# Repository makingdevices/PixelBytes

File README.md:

<!-- Improved compatibility of back to top link: See: https://github.com/othneildrew/Best-README-Template/pull/73 -->

<!--
*** Thanks for checking out the Best-README-Template. If you have a suggestion
*** that would make this better, please fork the repo and create a pull request
*** or simply open an issue with the tag "enhancement".
*** Don't forget to give the project a star!
*** Thanks again! Now go create something AMAZING! :D
-->

<!-- PROJECT SHIELDS -->
<!--
*** I'm using markdown "reference style" links for readability.
*** Reference links are enclosed in brackets [ ] instead of parentheses ( ).
*** See the bottom of this document for the declaration of the reference variables
*** for contributors-url, forks-url, etc. This is an optional, concise syntax you may use.
*** https://www.markdownguide.org/basic-syntax/#reference-style-links
-->
[![Instagram][ig-shield]][ig-url]
[![PCBWAY][sponsor-shield]][sponsor-url]
[![Stargazers][stars-shield]][stars-url]
[![Issues][issues-shield]][issues-url]
[![LinkedIn][linkedin-shield]][linkedin-url]

<!-- PROJECT LOGO -->
<br />
<div align="center">

<h3 align="center">Making Devices</h3>

  <p align="center">
    Open Source projects where we struggle with engineering, electronics, coding and who knows what else... Pixel Bytes is an evolution of my previous 8-bit console. The new version is based in the STM32F103CB with IC Leds for a colorwide screen and new power to code new games. 
  </p>
</div>

<!-- TABLE OF CONTENTS -->
<details>
  <summary>Table of Contents</summary>
  <ol>
    <li>
      <a href="#about-the-project">About The Project</a>
      <ul>
        <li><a href="#built-with">Built With</a></li>
      </ul>
    </li>
    <li>
      <a href="#Build-one">Build one</a>
      <ul>
      </ul>
    </li>
    <li><a href="#usage">Usage</a></li>
    <li><a href="#roadmap">Roadmap</a></li>
    <li><a href="#license">License</a></li>
    <li><a href="#contact">Contact</a></li>
    <li><a href="#Sponsor">Sponsor</a></li>
  </ol>
</details>

<!-- ABOUT THE PROJECT -->
## About The Project

[![Bytes Counter Shot][product-screenshot]](https://makingdevices.com/)

PixelBytes was born in colaboration with Wurth Elektronik and their new RGB IC LEDs. They sent me a bunch of them to test so I though of making a proper evolution of my previous video console. For this time, I wanted to test a new manufacturer for the microcontroller, so it is my first big project working with the STM32. Hopefully it will help to develop new exciting games as it is arduino-compatible. On top of that, I decided to add a giroscope sensor so we can add more ways to have fun within the gaming experience ;). 

The project is divided into two steps: 
1. The first one is the PixelBytesDisplay, which is a matrix of 13x21 IC LEDs divided in 6 strings. 
2. The second part is the host board, which will mount the microcontroller and all the battery and sensors.

<p align="right">(<a href="#readme-top">back to top</a>)</p>

### Built With

[![Microcontroller][PIC]][PIC-url]
[![Arduino][Arduino]][Arduino-url]
[![Kicad][kicad-shield]][kicad-url]
[![SPONSOR][wurth-icon]][sponsor-url-wurth]
[![SPONSOR][sponsor-icon]][sponsor-url]

<p align="right">(<a href="#readme-top">back to top</a>)</p>

<!-- GETTING STARTED -->

## Build one
The project is yet to be finished. Should you want to reproduce it, be careful. 

1. Get the gerber files for the latest version: [Pixel Bytes Display V0.1](/Gerber/Display/pixelbytesdisplay-v0.1) 
2. Get the gerber files for the latest version: [Pixel Bytes Host V0.1](/Gerber/Host/PixelBytesHostV0.1) 
3. Send them to a PCB manufacturer ([Our Sponsor is PCBWAY][sponsor-url])

YET TO BE COMPLETED.

<p align="right">(<a href="#readme-top">back to top</a>)</p>

<!-- USAGE EXAMPLES -->
## Usage

Instructions of use:

- When turn on, a menu is shown to select between the available games.
- Once you have played a game, a score board will appear everytime you open the game.
- You have a setting menu to turn-off the init splash and the sound.
- If you leave the console one minute without touching the buttons, it will turn into sleep mode.
- Enjoy!

<p align="right">(<a href="#readme-top">back to top</a>)</p>

<!-- ROADMAP -->
## Roadmap

- [x] Validate the Pixel Bytes Display
- [x] Assembly a prototype with the F103 Board
- [ ] Order/Assembly the Pixel Bytes Host
- [ ] Develop the firmware
  - [ ] Develop the library for the screen
  - [ ] Develop the menu 
  - [ ] Develop Snake
  - [ ] Develop Arkanoid
  - [ ] Develop Tetris
  - [ ] Develop a game that uses the gyro sensor
  - [ ] Score board
  - [ ] Sleep Mode
- [ ] Validate the complete design (host + display board)

See the [open issues](https://github.com/makingdevices/PixelBytes/issues) for a full list of proposed features (and known issues).

State: Project <b>ONGOING</b> - 22/09/2024

Priority: <b>High</b>

<p align="right">(<a href="#readme-top">back to top</a>)</p>

<!-- LICENSE -->
## License

Distributed under three licenses:
- [Hardware](/License/HW_cern_ohl_s_v2.pdf)
- [Software](/License/SW_GPLv3.0.txt)
- [Documentation](/License/Documentation_CC-BY-SA-4.0.txt)

OSHWA License: Not Finished

[![GPL v3 License][license-shield]][license-url] 
<p align="right">(<a href="#readme-top">back to top</a>)</p>

<!-- CONTACT -->
## Contact

Making Devices - [@MakingDevices](https://www.instagram.com/makingdevices/)

Project Link: [https://github.com/makingdevices/PixelBytes](https://github.com/makingdevices/PixelBytes)

Other Links: [LinkTree](https://makingdevices.com/links/)

<!-- Sponsor -->
## Sponsors
## PCBWAY

[PCBWAY](https://www.pcbway.com/?from=makingdevices) is the most professional PCB manufacturer for prototyping and low-volume production to work with in the world. With more than a decade in the field, They are committed to meeting the needs of their customers from different industries in terms of quality, delivery, cost-effectiveness and any other demanding requests. As Sponsor of Making Devices, they will be in charge of all the PCBs for MDV, allowing both of us to grow together in a long term partnership. We hope you take them into account for your both personal and professional prototypes or products.

[![Sponsor Shot][sponsor-pcb-1]][sponsor-url]
[![Sponsor Shot][sponsor-pcb-2]][sponsor-url]

## Würth Elektronik

[Wurth Elektronik](https://www.we-online.com/en) is one of the leading manufacturers of electronic and electromechanical components. The best I can say about them is to show you some pictures: All the LEDs from the board are from them. They also have buttons, resistors and capacitors that we use in all our PCBs. They also have some design kits with a lifetime refill which are amazing for makers and business so you can prototype on the go with a huge variety of components!

[![Sponsor Shot][sponsor-wurth-1]][sponsor-url-wurth]
[![Sponsor Shot][sponsor-wurth-3]][sponsor-url-wurth]

<p align="right">(<a href="#readme-top">back to top</a>)</p>

<!-- MARKDOWN LINKS & IMAGES -->
<!-- https://www.markdownguide.org/basic-syntax/#reference-style-links -->
[contributors-shield]: https://img.shields.io/github/contributors/makingdevices/PixelBytes.svg?style=for-the-badge
[contributors-url]: https://github.com/makingdevices/PixelBytes/graphs/contributors
[forks-shield]: https://img.shields.io/github/forks/makingdevices/PixelBytes.svg?style=for-the-badge
[forks-url]: https://github.com/makingdevices/PixelBytes/network/members
[stars-shield]: https://img.shields.io/github/stars/makingdevices/PixelBytes.svg?style=for-the-badge
[stars-url]: https://github.com/makingdevices/PixelBytes/stargazers
[issues-shield]: https://img.shields.io/github/issues/makingdevices/PixelBytes.svg?style=for-the-badge
[issues-url]: https://github.com/makingdevices//PixelBytes/issues
[license-shield]: /images/license.png
[license-url]: https://github.com/makingdevices/PixelBytes/tree/main/License
[linkedin-shield]: https://img.shields.io/badge/-LinkedIn-black.svg?style=for-the-badge&logo=linkedin&colorB=555
[linkedin-url]: https://www.linkedin.com/company/making-devices/
[sponsor-shield]: https://img.shields.io/badge/SPONSOR-PCBWAY-black.svg?style=for-the-badge&colorB=1200
[sponsor-url]: https://www.pcbway.com/?from=makingdevices
[sponsor-screenshot]: /images/PCB_sponsor.png
[sponsor-pcb-1]: /images/pixelbytes_pcb1.JPG
[sponsor-pcb-2]: /images/pixelbytes_pcb2.JPG
[sponsor-wurth-1]: /images/wurth_1.gif
[sponsor-wurth-3]: /images/wurth_3.jpg
[sponsor-url-wurth]: https://www.we-online.com/en
[product-screenshot]: images/screenshot.gif
[PIC]: https://img.shields.io/badge/STM32F103-0000D1?style=for-the-badge
[PIC-url]: https://www.st.com/en/microcontrollers-microprocessors/stm32f103.html
[kicad-shield]: https://img.shields.io/badge/kicad-0b03fc?style=for-the-badge&logo=kicad&logoColor=white
[kicad-url]: https://www.kicad.org/
[YT-screenshot]: images/YT_assembly.PNG
[sponsor-icon]:  https://img.shields.io/badge/-PCBWAY-black.svg?style=for-the-badge&colorB=1200
[ig-shield]: https://img.shields.io/badge/instagram-a83297?style=for-the-badge&logo=instagram&logoColor=white
[ig-url]: https://www.instagram.com/makingdevices/
[MPLAB-C]: https://img.shields.io/badge/MPLAB%20C18-DD0031?style=for-the-badge&logo=C&logoColor=white
[Arduino]: https://img.shields.io/badge/ARDUINO-00878F?style=for-the-badge&logo=arduino&logoColor=white
[wurth-icon]: https://img.shields.io/badge/Wurth%20elektronik-FF0031?style=for-the-badge&logoColor=white
[Arduino-url]: https://www.arduino.cc/
[MPLAB-C-url]: https://www.microchip.com/en-us/development-tool/SW006011
[Svelte.dev]: https://img.shields.io/badge/Svelte-4A4A55?style=for-the-badge&logo=svelte&logoColor=FF3E00
[Svelte-url]: https://svelte.dev/
[Laravel.com]: https://img.shields.io/badge/Laravel-FF2D20?style=for-the-badge&logo=laravel&logoColor=white
[Laravel-url]: https://laravel.com
[Bootstrap.com]: https://img.shields.io/badge/Bootstrap-563D7C?style=for-the-badge&logo=bootstrap&logoColor=white
[Bootstrap-url]: https://getbootstrap.com
[JQuery.com]: https://img.shields.io/badge/jQuery-0769AD?style=for-the-badge&logo=jquery&logoColor=white
[JQuery-url]: https://jquery.com

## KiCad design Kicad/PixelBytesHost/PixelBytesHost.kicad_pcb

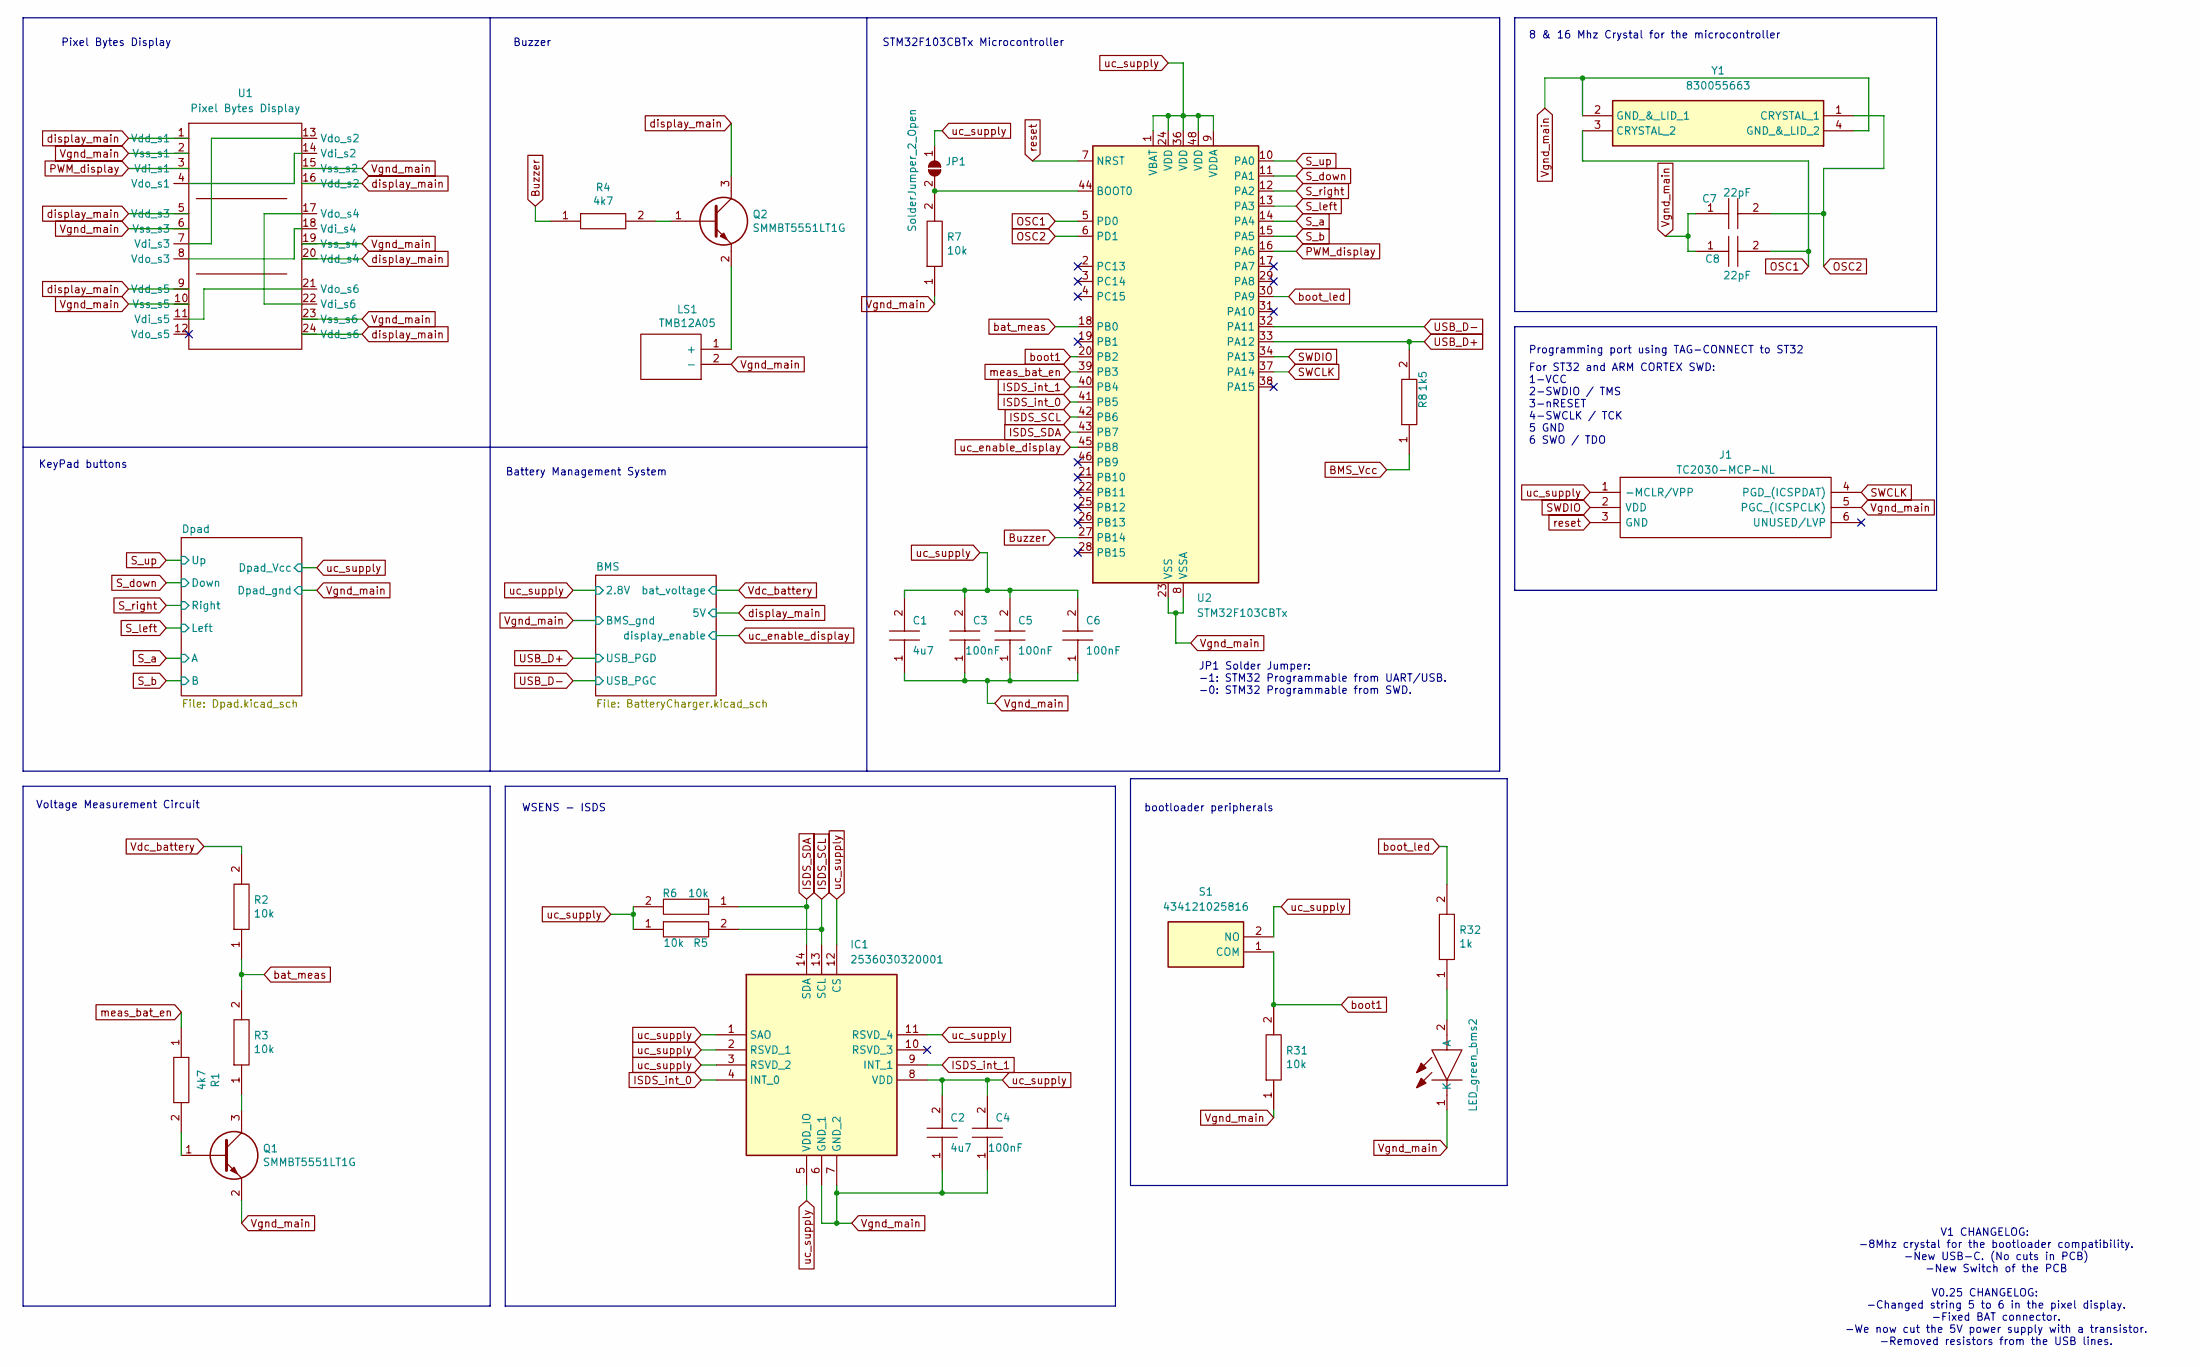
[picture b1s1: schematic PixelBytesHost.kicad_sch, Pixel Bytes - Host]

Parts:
C1, C2: 4u7; CAPC2012X140N; Manufacturer_Part_Number C0805C475M8RACTU
C3, C4, C5, C6: 100nF; CAPC2012X140N; Manufacturer_Part_Number C0805C475M8RACTU
C7, C8: 22pF; C_0805_2012Metric; Manufacturer_Part_Number GCG21BR71H154KA01K
IC1: 2536030320001; Mouser Part Number 710-2536030320001
J1: TC2030-MCP-NL; Manufacturer_Part_Number TC2030-MCP-NL
JP1: SolderJumper_2_Open; SolderJumper-2_P1.3mm_Open_RoundedPad1.0x1.5mm
LED_green_bms2: LTST-C171GKT; LEDC2012X90N; Manufacturer_Part_Number LTST-C171GKT
LS1: TMB12A05; Manufacturer_Part_Number TMB12A05
Q1, Q2: SMMBT5551LT1G; SOT96P237X111-3N; Manufacturer_Part_Number SMMBT5551LT1G
R1, R4: 4k7; RESC2012X65N; Manufacturer_Part_Number KTR10EZPF4220
R2, R3, R5, R6, R7, R31: 10k; R_0805_2012Metric; Manufacturer_Part_Number ERJP6WF1303V
R8: 1k5; R_0805_2012Metric; Manufacturer_Part_Number ERJP6WF1303V
R32: 1k; R_0805_2012Metric; Manufacturer_Part_Number ERJP6WF1303V
S1: 434121025816; 434121050816; Manufacturer_Part_Number 434121025816; Mouser Part Number 710-434121025816
U1: Pixel Bytes Display; pixelbytesdisplay
U2: STM32F103CBTx; LQFP-48_7x7mm_P0.5mm
Y1: 830055663; Mouser Part Number 710-830055663

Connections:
BMS_Vcc: R8.1; also elsewhere on the board
Buzzer: R4.1, U2.27 (PB14)
ISDS_SCL: IC1.13 (SCL), R5.2, U2.42 (PB6)
ISDS_SDA: IC1.14 (SDA), R6.1, U2.43 (PB7)
ISDS_int_0: IC1.4 (INT_0), U2.41 (PB5)
ISDS_int_1: IC1.9 (INT_1), U2.40 (PB4)
unnamed: JP1.2 (B), R7.2, U2.44 (BOOT0)
unnamed: LED_green_bms2.2 (A), R32.1
unnamed: LS1.1 (+), Q2.2
unnamed: Q1.1, R1.2
unnamed: Q1.3, R3.1
unnamed: Q2.1, R4.2
unnamed: U1.4 (Vdo_s1), U1.14 (Vdi_s2)
unnamed: U1.7 (Vdi_s3), U1.13 (Vdo_s2)
unnamed: U1.8 (Vdo_s3), U1.18 (Vdi_s4)
unnamed: U1.11 (Vdi_s5), U1.21 (Vdo_s6)
unnamed: U1.17 (Vdo_s4), U1.22 (Vdi_s6)
OSC1: C8.2, U2.5 (PD0), Y1.3 (CRYSTAL_2)
OSC2: C7.2, U2.6 (PD1), Y1.1 (CRYSTAL_1)
PWM_display: U1.3 (Vdi_s1), U2.16 (PA6)
SWCLK: J1.4 (PGD_(ICSPDAT)), U2.37 (PA14)
SWDIO: J1.2 (VDD), U2.34 (PA13)
S_a: U2.14 (PA4); also elsewhere on the board
S_b: U2.15 (PA5); also elsewhere on the board
S_down: U2.11 (PA1); also elsewhere on the board
S_left: U2.13 (PA3); also elsewhere on the board
S_right: U2.12 (PA2); also elsewhere on the board
S_up: U2.10 (PA0); also elsewhere on the board
USB_D+: R8.2, U2.33 (PA12); also elsewhere on the board
USB_D-: U2.32 (PA11); also elsewhere on the board
Vdc_battery: R2.2; also elsewhere on the board
Vgnd_main: C1.1, C2.1, C3.1, C4.1, C5.1, C6.1, C7.1, C8.1, IC1.6 (GND_1), IC1.7 (GND_2), J1.5 (PGC_(ICSPCLK)), LED_green_bms2.1 (K), LS1.2 (-), Q1.2, R7.1, R31.1, U1.2 (Vss_s1), U1.6 (Vss_s3), U1.10 (Vss_s5), U1.15 (Vss_s2), U1.19 (Vss_s4), U1.23 (Vss_s6), U2.8 (VSSA), U2.23 (VSS), U2.35 (VSS), U2.47 (VSS), Y1.2 (GND_&_LID_1), Y1.4 (GND_&_LID_2); also elsewhere on the board
bat_meas: R2.1, R3.2, U2.18 (PB0)
boot1: R31.2, S1.1 (COM), U2.20 (PB2)
boot_led: R32.2, U2.30 (PA9)
meas_bat_en: R1.1, U2.39 (PB3)
reset: J1.3 (GND), U2.7 (NRST)
uc_enable_display: U2.45 (PB8); also elsewhere on the board
uc_supply: C1.2, C2.2, C3.2, C4.2, C5.2, C6.2, IC1.1 (SAO), IC1.2 (RSVD_1), IC1.3 (RSVD_2), IC1.5 (VDD_IO), IC1.8 (VDD), IC1.11 (RSVD_4), IC1.12 (CS), J1.1 (-MCLR/VPP), JP1.1 (A), R5.1, R6.2, S1.2 (NO), U2.1 (VBAT), U2.9 (VDDA), U2.24 (VDD), U2.36 (VDD), U2.48 (VDD); also elsewhere on the board

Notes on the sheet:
KeyPad buttons
Battery Management System
JP1 Solder Jumper: -1: STM32 Programmable from UART/USB. -0: STM32 Programmable from SWD.
WSENS - ISDS
V1 CHANGELOG: -8Mhz crystal for the bootloader compatibility. -New USB-C. (No cuts in PCB) -New Switch of the PCB V0.25 CHANGELOG: -Changed string 5 to 6 in the pixel display. -Fixed BAT connector. -We now cut the 5V power supply with a transistor. -Removed resistors from the USB lines.
Programming port using TAG-CONNECT to ST32
8 & 16 Mhz Crystal for the microcontroller
Pixel Bytes Display
bootloader peripherals
Buzzer
For ST32 and ARM CORTEX SWD: 1-VCC 2-SWDIO / TMS 3-nRESET 4-SWCLK / TCK 5 GND 6 SWO / TDO
STM32F103CBTx Microcontroller
Voltage Measurement Circuit

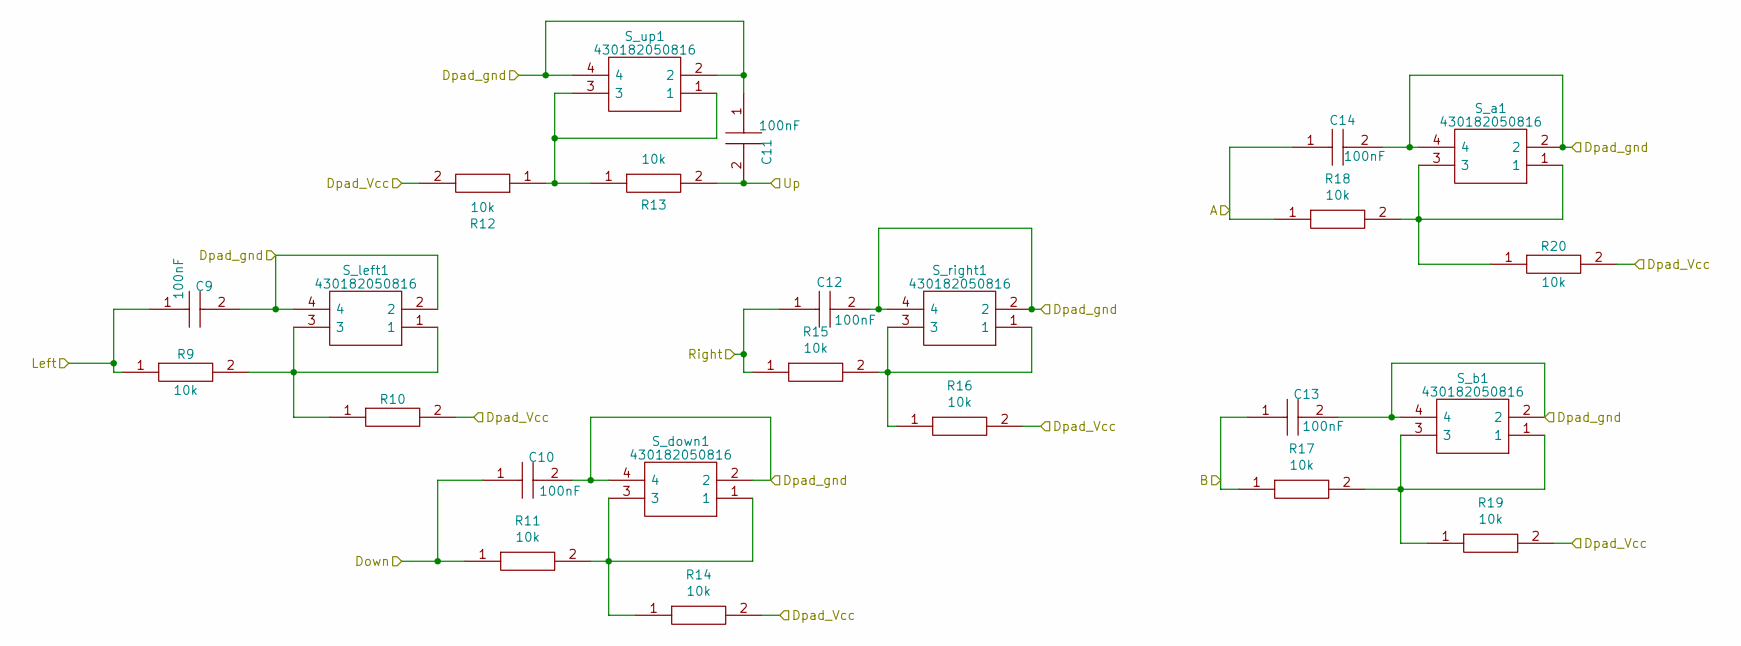
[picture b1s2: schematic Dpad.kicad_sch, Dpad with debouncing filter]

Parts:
C9, C10, C11, C12, C13, C14: 100nF; CAPC2012X140N; Manufacturer_Part_Number GCG21BR71H154KA01K
R9, R10, R11, R12, R13, R14, R15, R16, R17, R18, R19, R20: 10k; R_0805_2012Metric; Manufacturer_Part_Number KTR10EZPF4220
S_a1: 430182050816; 430182070816; Mouser Part Number 710-430182050816
S_b1: 430182050816; 430182070816; Mouser Part Number 710-430182050816
S_down1: 430182050816; 430182070816; Mouser Part Number 710-430182050816
S_left1: 430182050816; 430182070816; Mouser Part Number 710-430182050816
S_right1: 430182050816; 430182070816; Mouser Part Number 710-430182050816
S_up1: 430182050816; 430182070816; Mouser Part Number 710-430182050816

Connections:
unnamed: R9.2, R10.1, S_left1.1, S_left1.3
unnamed: R11.2, R14.1, S_down1.1, S_down1.3
unnamed: R12.1, R13.1, S_up1.1, S_up1.3
unnamed: R15.2, R16.1, S_right1.1, S_right1.3
unnamed: R17.2, R19.1, S_b1.1, S_b1.3
unnamed: R18.2, R20.1, S_a1.1, S_a1.3
S_a: C14.1, R18.1; also elsewhere on the board
S_b: C13.1, R17.1; also elsewhere on the board
S_down: C10.1, R11.1; also elsewhere on the board
S_left: C9.1, R9.1; also elsewhere on the board
S_right: C12.1, R15.1; also elsewhere on the board
S_up: C11.2, R13.2; also elsewhere on the board
Vgnd_main: C9.2, C10.2, C11.1, C12.2, C13.2, C14.2, S_a1.2, S_a1.4, S_b1.2, S_b1.4, S_down1.2, S_down1.4, S_left1.2, S_left1.4, S_right1.2, S_right1.4, S_up1.2, S_up1.4; also elsewhere on the board
uc_supply: R10.2, R12.2, R14.2, R16.2, R19.2, R20.2; also elsewhere on the board

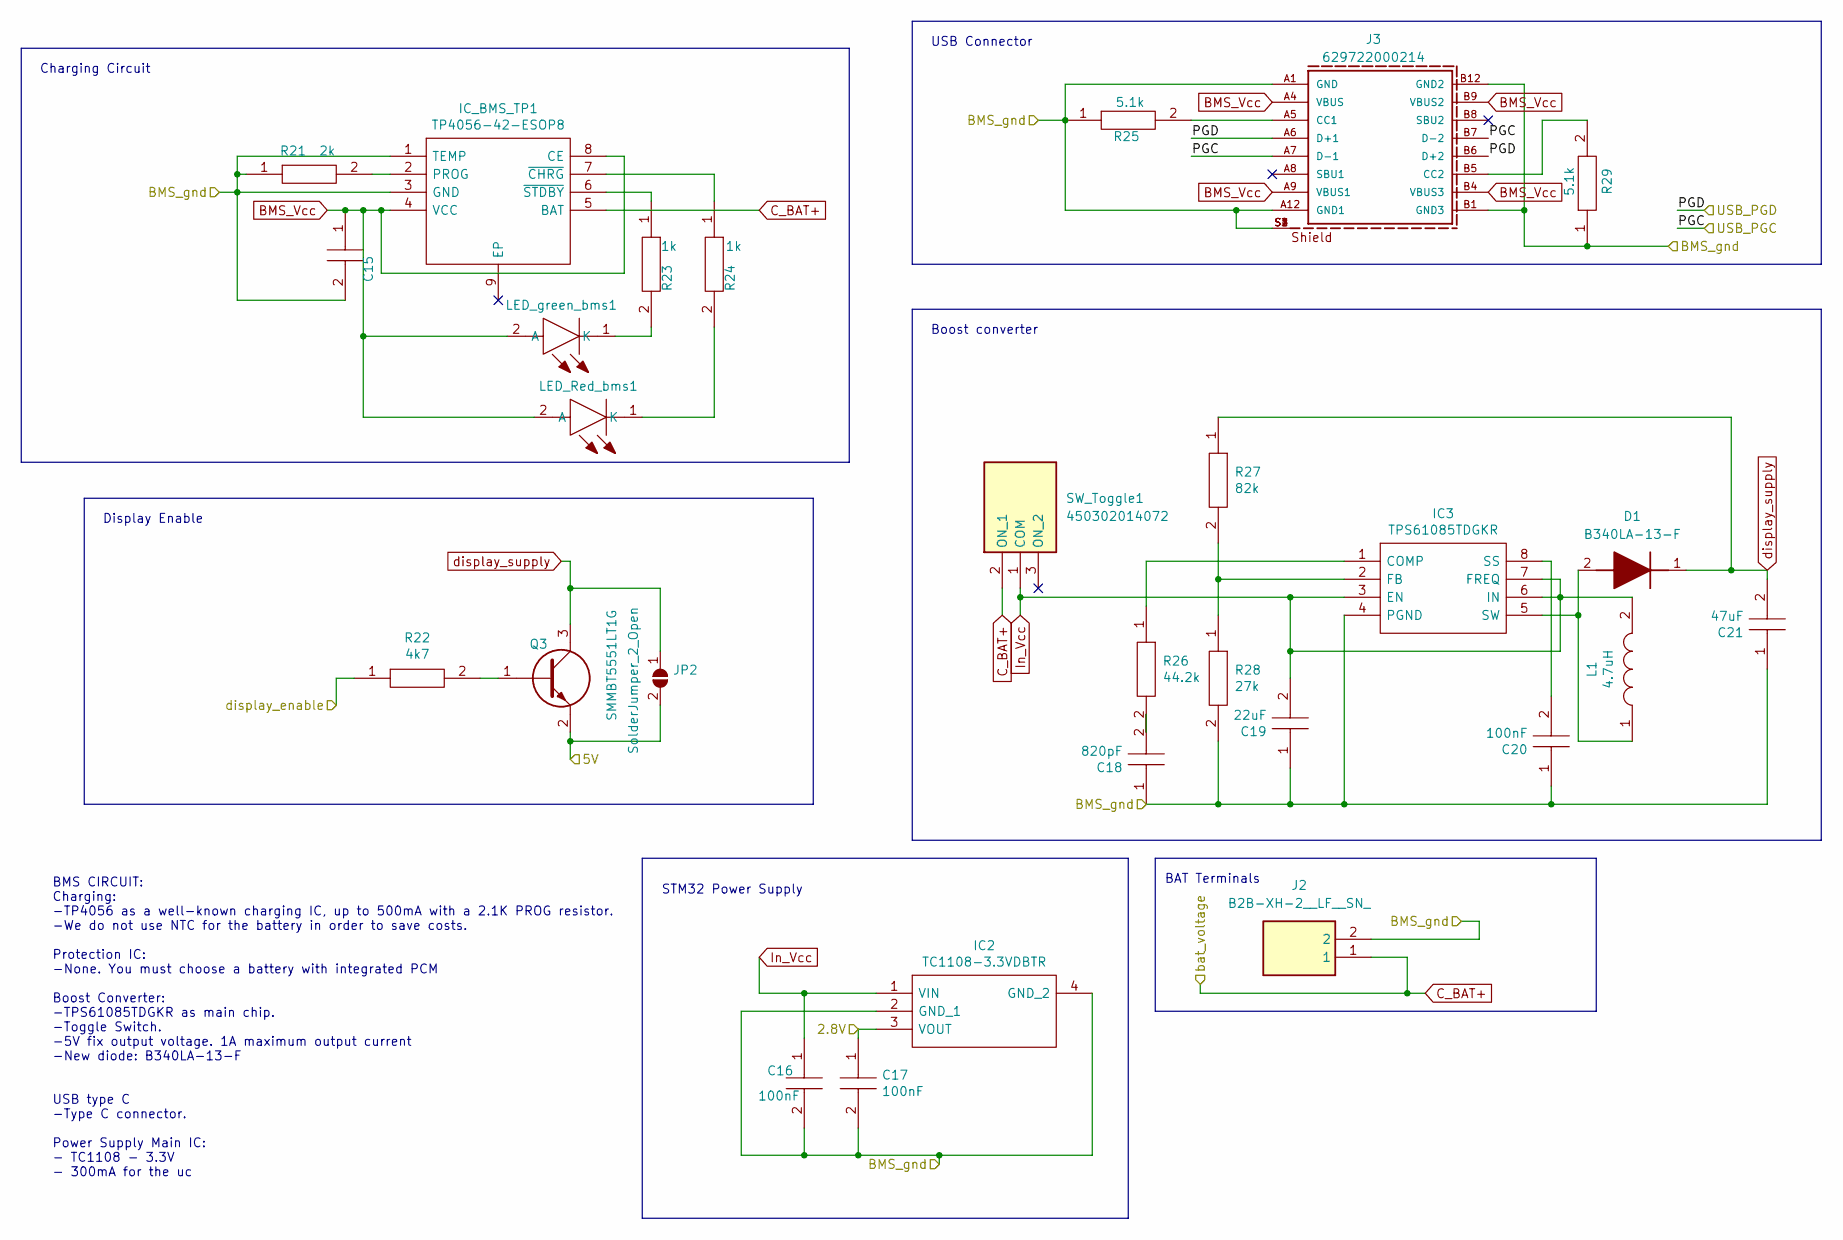
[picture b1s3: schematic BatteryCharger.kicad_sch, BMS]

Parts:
C15: 10uF; CAPC2012X145N; Manufacturer_Part_Number GCG21BR71H154KA01K
C16, C17, C20: 100nF; CAPC2012X140N; Manufacturer_Part_Number C0805C475M8RACTU
C18: 820pF; CAPC2012X140N; Manufacturer_Part_Number C0805C475M8RACTU
C19: 22uF; CAPC2012X140N; Manufacturer_Part_Number C0805C475M8RACTU
C21: 47uF; CAPC2012X140N; Manufacturer_Part_Number C0805C475M8RACTU
D1: B340LA-13-F; DIOM5226X240N; Mouser Part Number 621-B340LA-F
IC2: TC1108-3.3VDBTR; SOT230P700X180-4N; Manufacturer_Part_Number TC1108-3.3VDBTR
IC3: TPS61085TDGKR; SOP65P490X110-8N; Mouser Part Number 595-TPS61085TDGKR
IC_BMS_TP1: TP4056-42-ESOP8; SOIC127P600X175-9N; Manufacturer_Part_Number TP4056-42-ESOP8
J2: B2B-XH-2__LF__SN_; B2BXH2LFSN; Manufacturer_Part_Number B2B-XH-2 (LF)(SN)
J3: 629722000214; PART-NUMBER 629722000214
JP2: SolderJumper_2_Open; SolderJumper-2_P1.3mm_Open_RoundedPad1.0x1.5mm
L1: 4.7uH; SRN6045_1; Mouser Part Number 652-SRN6045-4R7Y
LED_Red_bms1: LTST-C171GKT; LEDC2012X90N; Manufacturer_Part_Number LTST-C171GKT
LED_green_bms1: LTST-C171GKT; LEDC2012X90N; Manufacturer_Part_Number LTST-C171GKT
Q3: SMMBT5551LT1G; SOT96P237X111-3N; Manufacturer_Part_Number SMMBT5551LT1G
R21: 2k; RESC2012X65N; Manufacturer_Part_Number KTR10EZPF4220
R22: 4k7; RESC2012X65N; Manufacturer_Part_Number KTR10EZPF4220
R23, R24: 1k; RESC2012X65N; Manufacturer_Part_Number KTR10EZPF4220
R25, R29: 5.1k; RESC2012X65N; Manufacturer_Part_Number KTR10EZPF4220
R26: 44.2k; RESC2012X75N; Manufacturer_Part_Number ERJP6WF1303V
R27: 82k; RESC2012X75N; Manufacturer_Part_Number ERJP6WF1303V
R28: 27k; RESC2012X75N; Manufacturer_Part_Number ERJP6WF1303V
SW_Toggle1: 450302014072; Mouser Part Number 710-450302014072

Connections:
BMS_Vcc: C15.1, IC_BMS_TP1.4 (VCC), IC_BMS_TP1.8 (CE), J3.A4 (VBUS), J3.A9 (VBUS1), J3.B4 (VBUS3), J3.B9 (VBUS2), LED_Red_bms1.2 (A), LED_green_bms1.2 (A); also elsewhere on the board
In_Vcc: C16.1, C19.2, IC2.1 (VIN), IC3.3 (EN), IC3.6 (IN), IC3.7 (FREQ), L1.2, SW_Toggle1.1 (COM)
unnamed: C18.2, R26.2
unnamed: D1.2 (A), IC3.5 (SW), L1.1
unnamed: IC3.1 (COMP), R26.1
unnamed: IC3.2 (FB), R27.2, R28.1
unnamed: C20.2, IC3.8 (SS)
unnamed: IC_BMS_TP1.2 (PROG), R21.2
unnamed: IC_BMS_TP1.7 (~CHRG), R24.1
unnamed: IC_BMS_TP1.6 (~STDBY), R23.1
unnamed: J3.A5 (CC1), R25.2
unnamed: J3.B5 (CC2), R29.2
unnamed: LED_Red_bms1.1 (K), R24.2
unnamed: LED_green_bms1.1 (K), R23.2
unnamed 25: Q3.1 (B), R22.2; also elsewhere on the board
USB_D+: J3.A6 (D+1), J3.B6 (D+2); also elsewhere on the board
USB_D-: J3.A7 (D-1), J3.B7 (D-2); also elsewhere on the board
Vdc_battery: IC_BMS_TP1.5 (BAT), J2.1, SW_Toggle1.2 (ON_1); also elsewhere on the board
Vgnd_main: C15.2, C16.2, C17.2, C18.1, C19.1, C20.1, C21.1, IC2.2 (GND_1), IC2.4 (GND_2), IC3.4 (PGND), IC_BMS_TP1.1 (TEMP), IC_BMS_TP1.3 (GND), J2.2, J3.A1 (GND), J3.A12 (GND1), J3.B1 (GND3), J3.B12 (GND2), J3.S1, J3.S2, J3.S3, J3.S4, R21.1, R25.1, R28.2, R29.1; also elsewhere on the board
uc_enable_display: R22.1; also elsewhere on the board
uc_supply: C17.1, IC2.3 (VOUT); also elsewhere on the board

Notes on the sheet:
Boost converter
BMS CIRCUIT: Charging: -TP4056 as a well-known charging IC, up to 500mA with a 2.1K PROG resistor. -We do not use NTC for the battery in order to save costs. Protection IC: -None. You must choose a battery with integrated PCM Boost Converter: -TPS61085TDGKR as main chip. -Toggle Switch. -5V fix out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
Display Enable
USB Connector
STM32 Power Supply
BAT Terminals
Charging Circuit

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
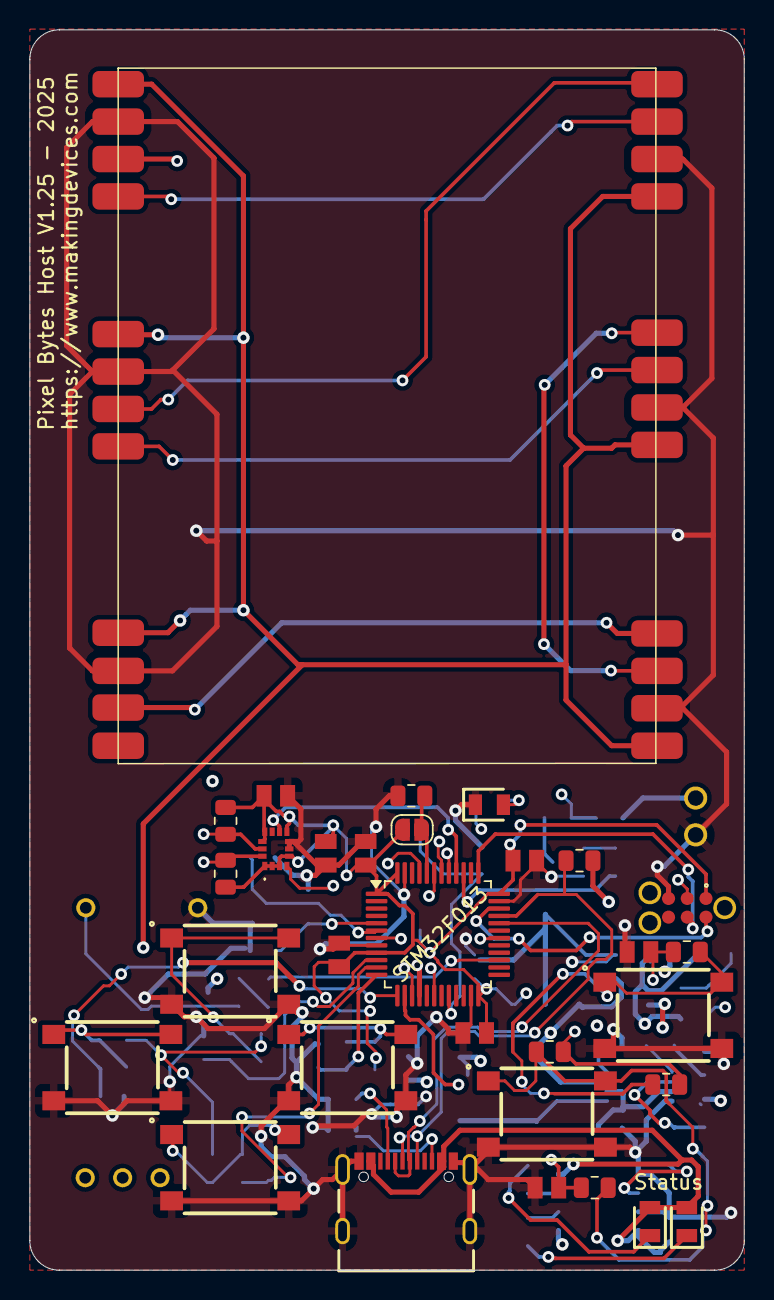
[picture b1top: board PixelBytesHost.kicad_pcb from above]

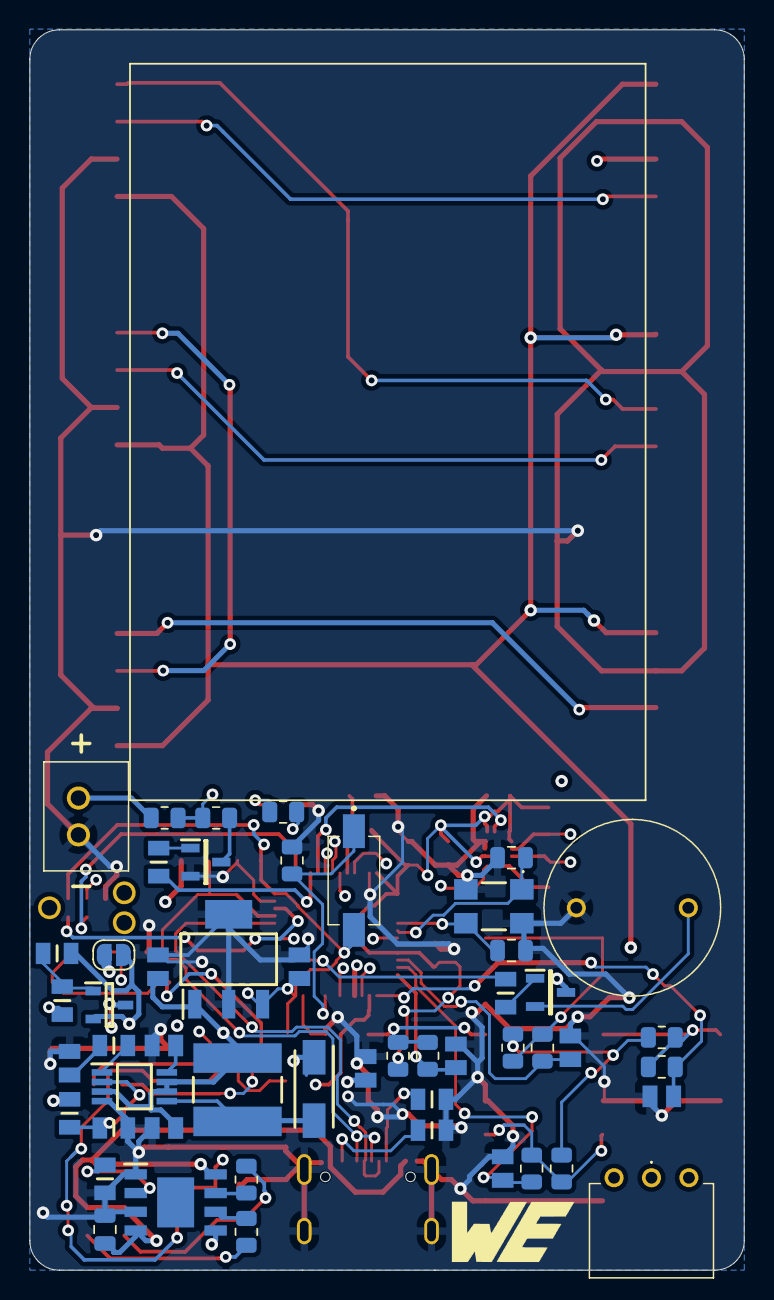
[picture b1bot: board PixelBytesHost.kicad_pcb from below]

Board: 4 copper layers, 48.5 x 84.2 mm, 82 parts (51 on the bottom side), 61 nets.

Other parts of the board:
R30: 3k3; RESC2012X65N

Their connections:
unnamed 25: R30.1; also elsewhere on the board

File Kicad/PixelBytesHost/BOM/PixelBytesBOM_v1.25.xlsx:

Designator | Value | Package | Notes | Manufacturer / Distributor | Part number | Total | Price | Total Price | Link to distributor
C1,C2 | 4.7 µF | 0805 | - | Würth Elektronik | 885012207053 | 2 |  | 0
C3,C4,C5,C6,C9,C10,C11,C12,C13,C14,C16,C17,C20 | 100 nF | 0805 | - | Würth Elektronik | 885012207045 | 13 |  | 0
C7,C8 | 22 pF | 0805 | - | Würth Elektronik | 885012007012 | 2 |  | 0
C15 | 10 µF | 0805 | - | Würth Elektronik | 885012107014 | 1 |  | 0
C18 | 820 pF | 0805 | - | Mouser | 581-0805YC821KAT2A | 1 | 0.26 | 0.26 | https://www.mouser.de/ProductDetail/KYOCERA-AVX/0805YC821KAT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
C19 | 22 µF | 0805 | - | Würth Elektronik | 885012107011 | 1 |  | 0
C21 | 47 µF | 0805 | - | Würth Elektronik | 885012107006 | 1 |  | 0
D1 |  | SMA-2 | - | Mouser | 621-B340LA-F | 1 | 0.40899999999999997 | 0.40899999999999997 | https://www.mouser.de/ProductDetail/Diodes-Incorporated/B340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
IC1 |  |  | - | Würth Elektronik | 2536030320001 | 1 |  | 0
IC2 |  | SOT-223-3 | - | Mouser | 579-TC1108-3.3VDBTR | 1 |  | 0 | https://www.mouser.de/ProductDetail/Microchip-Technology/TC1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
IC3 |  | VSSOP-8 | - | Mouser | TPS61085TDGKR | 1 | 2.09 | 2.09 | https://www.mouser.de/ProductDetail/Texas-Instruments/TPS610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
IC_BMS_TP1 |  |  | TP4056 | LCSC | TP4056-42-ESOP8 | 1 |  | 0
J1 |  |  | TC2030-MCP-NL | RS |  | 1 |  | 0 | http://uk.rs-online.com/web/p/products/8252561
J3 |  | USB 2.0 Type C | - | Würth Elektronik | 629722000214 | 1 |  | 0
J2 |  |  | Depends on the battery! | Digikey | B2B-PH-K-S(LF)(SN) | 1 | 0.11 | 0.11 | https://eu.mouser.com/ProductDetail/JST-Commercial/B2B-PH-K-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
JP1,JP2 |  |  | Do not solder JP1 -> reset the microcontroller. JP2 -> It turns ON the display 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 |  |  | 2 |  | 0
L1 | 4.7 µH | 6045 | - | Würth Elektronik | 74404064470 | 1 |  | 0
LED_green_bms1, LED_green_bms2 |  | 0805 | - | Würth Elektronik | 150080VS75000 | 2 |  | 0
LED_Red_bms1 |  | 0805 | - | Würth Elektronik | 150080RS75000 | 1 |  | 0
LS1 |  | 12 mm x 9.5 mm THT |  | Mouser | 497-IE122305-7 | 1 | 1.84 | 1.84
Q1,Q2 |  | SOT-23-3 | - | Mouser | 863-SMMBT5551LT1G | 2 | 0.17699999999999999 | 0.35399999999999998 | https://www.mouser.de/ProductDetail/onsemi/SMMBT5551LT1G?qs=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
Q3 |  | SOT-23-3 | - | Mouser | PBSS5160T-QR | 1 | 0.36099999999999999 | 0.36099999999999999 | https://eu.mouser.com/ProductDetail/Nexperia/PBSS5160T-QR?qs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
R1,R4 | 4.7 k | 0805 | - | Mouser | 652-CRS0805FX4701ELF | 2 | 0.19500000000000001 | 0.39 | https://www.mouser.de/ProductDetail/Bourns/CRS0805-FX-4701EL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
R8 | 1.5 k | 0805 | - | Mouser | 603-AC0805FR-7W1K5L | 1 | 0.121 | 0.121 | https://www.mouser.de/ProductDetail/YAGEO/AC0805FR-7W1K5L?qs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
R2, R3, R5, R6, R7, R9, R10, R11, R12, R13, R14, R15, R16, R17, R18, R19, R20, 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 | 10 k | 0805 | - | Würth Elektronik | 560112120004 | 18 |  | 0
R30 | 3K3 | 0805 | - | Würth Elektronik | 560112120029 | 1 |  | 0
R21 | 2 k | 0805 | - | Mouser | 71-RCC08052K00FKEA | 1 | 0.16700000000000001 | 0.16700000000000001 | https://www.mouser.de/ProductDetail/Vishay-Dale/RCC08052K00F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
R22 | 6k8 | 0805 |  | Würth Elektronik | 560112120031 | 1
R23,R24, R32 | 1 k | 0805 | - | Mouser | 652-CRS0805FX1001ELF | 3 | 0.19500000000000001 | 0.58499999999999996 | https://www.mouser.de/ProductDetail/Bourns/CRS0805-FX-1001EL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
R25,R29 | 5.1 k | 0805 | - | Würth Elektronik | 560112120019 | 2 |  | 0
R26 | 44.2 k | 0805 | - | Mouser | 660-RK73H2ATTD4422F | 1 | 0.10100000000000001 | 0.10100000000000001 | https://www.mouser.de/ProductDetail/KOA-Speer/RK73H2ATTD4422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
R27 | 100 k | 0805 |  | Würth Elektronik | 560112120013 | 1
R28 | 38,3 k | 0805 |  | Mouser | CR0805-FX-3832ELF | 1 | 9.5000000000000001E-2 | 9.5000000000000001E-2 | https://eu.mouser.com/ProductDetail/Bourns/CR0805-FX-3832ELF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
SW_Toggle1 |  |  |  | Würth Elektronik | 450302014072 | 1 |  | 0
S_a1,S_b1,S_down1,S_left1,S_right1,S_up1 |  | 6x6 mm |  | Würth Elektronik | 430182050816 | 6 |  | 0
S1 |  |  |  | Würth Elektronik | 434121025816 | 1 |  | 0
U1 | Pixel Bytes Display | - | - | - | - | 1 |  | 0
U2 |  | LQFP-48 |  | Mouser | 511-STM32F103CBT6TR | 1 | 5.78 | 5.78 | https://eu.mouser.com/ProductDetail/STMicroelectronics/STM32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
Y1 | 8Mhz |  |  | Würth Elektronik | 830055663 | 1 |  | 0
 |  |  |  |  | Total | 82 |  | 12.662999999999998
Tested Battery: | https://www.amazon.com/EEMB-1100mAh-Battery-Rechargeable-Con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

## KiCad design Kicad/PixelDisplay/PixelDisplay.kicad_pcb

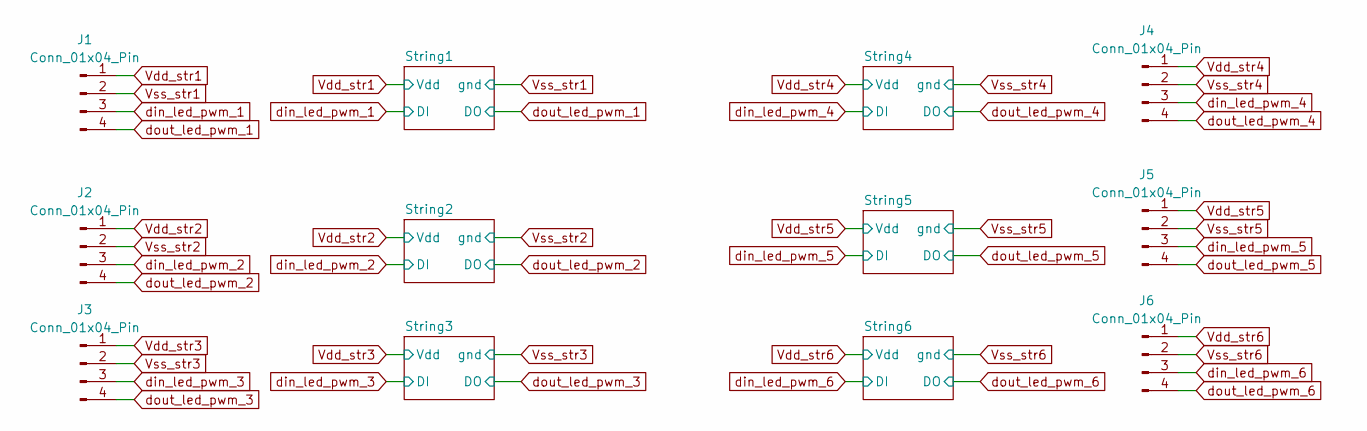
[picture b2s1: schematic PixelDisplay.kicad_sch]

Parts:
J1, J2, J3, J4, J5, J6: Conn_01x04_Pin; castellated_4x2.54mm

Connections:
Vdd_str1: J1.1; also elsewhere on the board
Vdd_str2: J2.1; also elsewhere on the board
Vdd_str3: J3.1; also elsewhere on the board
Vdd_str4: J4.1; also elsewhere on the board
Vdd_str5: J5.1; also elsewhere on the board
Vdd_str6: J6.1; also elsewhere on the board
Vss_str1: J1.2; also elsewhere on the board
Vss_str2: J2.2; also elsewhere on the board
Vss_str3: J3.2; also elsewhere on the board
Vss_str4: J4.2; also elsewhere on the board
Vss_str5: J5.2; also elsewhere on the board
Vss_str6: J6.2; also elsewhere on the board
din_led_pwm_1: J1.3; also elsewhere on the board
din_led_pwm_2: J2.3; also elsewhere on the board
din_led_pwm_3: J3.3; also elsewhere on the board
din_led_pwm_4: J4.3; also elsewhere on the board
din_led_pwm_5: J5.3; also elsewhere on the board
din_led_pwm_6: J6.3; also elsewhere on the board
dout_led_pwm_1: J1.4; also elsewhere on the board
dout_led_pwm_2: J2.4; also elsewhere on the board
dout_led_pwm_3: J3.4; also elsewhere on the board
dout_led_pwm_4: J4.4; also elsewhere on the board
dout_led_pwm_5: J5.4; also elsewhere on the board
dout_led_pwm_6: J6.4; also elsewhere on the board
